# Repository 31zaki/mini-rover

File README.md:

# Rover mini Project

This project, named "rover-mini," is inspired by my favorite British car, the [Rover Mini](https://en.wikipedia.org/wiki/Mini). The name reflects my respect for this iconic vehicle, known for its compact design and efficient performance, traits that I aim to emulate in this mini robotic rover project.

## Project Overview
The Mini Rover is built using only the chassis of the PiCar-X. For detailed information about the PiCar-X chassis, you can refer to the [official documentation](https://docs.sunfounder.com/projects/picar-x-v20/en/latest/index.html). Note that in this project, the included Robot-HAT is not used. Instead, a custom PCB has been designed for the necessary components and connections. Additionally, custom parts for mounting the PCB were designed using Fusion360.

## Components

- **Raspberry Pi 4B** running Ubuntu Server 22.04 Jazzy.
- **Chassis:** PiCar-X (excluding Robot-HAT expansion board).
- **Cooling:** [GeeekPi Raspberry Pi Low Profile CPU Cooler](https://www.amazon.co.jp/-/en/GeeekPi-Raspberry-Profile-Compatible-Heatsink/dp/B082WV2LL7?th=1).
- **Battery:** [Battery for Raspberry Pi](https://www.amazon.co.jp/gp/product/B0C1GFX5LW/ref=ppx_yo_dt_b_asin_title_o00_s02?ie=UTF8&psc=1).
- **GPIO Expansion:** [GPIO Expansion Board](https://www.amazon.co.jp/gp/product/B072XBX3XX/ref=ppx_yo_dt_b_asin_title_o00_s01?ie=UTF8&th=1).
- **Breadboard** for initial wiring, with plans to design a custom PCB later.

## PCB Design

To streamline the wiring and improve reliability, a custom PCB has been designed using EAGLE. The PCB integrates all necessary components and connections for the Mini Rover.

### EAGLE Design Files

The PCB design files can be found in the `EAGLE/project` directory of this repository. This includes:
- Schematic file (`main_board.sch`)
- Board file (`main_board.brd`)

### EAGLE Libraries

Custom EAGLE libraries have been created for the components used in this project. These libraries are included in the `EAGLE/libraries` directory of this repository.

## Development Environment

**Programming Language:** Python
- **IDE:** Visual Studio Code (VSCode)
- **Connection:** SSH from VSCode to Raspberry Pi

## Wiring Information

### Raspberry Pi 4 (40-pin header) Connections
- **3.3V (Pin 1)** --------------- VCC (BNO055)
- **5V (Pin 2)** --------------- VCC (HC-SR04)
- **GND (Pin 6)** --------------- GND (L298N)
- **GND (Pin 9)** --------------- GND (BNO055)
- **GND (Pin 14)** -------------- GND (Servo Motors)
- **GPIO 2 (Pin 3)** ------------- SDA (BNO055)
- **GPIO 3 (Pin 5)** ------------- SCL (BNO055)
- **GPIO 4 (Pin 7)** ------------- ECHO (HC-SR04) through voltage divider
- **GPIO 17 (Pin 11)** ----------- TRIG (HC-SR04)
- **GPIO 18 (Pin 12)** ----------- ENA (L298N)
- **GPIO 23 (Pin 16)** ----------- IN2 (L298N)
- **GPIO 24 (Pin 18)** ----------- IN1 (L298N)
- **GPIO 25 (Pin 22)** ----------- ENB (L298N)
- **GPIO 27 (Pin 13)** ----------- IN3 (L298N)
- **GPIO 22 (Pin 15)** ----------- IN4 (L298N)
- **GPIO 5 (Pin 29)** ------------ Servo 1 Control
- **GPIO 6 (Pin 31)** ------------ Servo 2 Control
- **GPIO 13 (Pin 33)** ----------- Servo 3 Control

## Goals

- **Programming Practice:** Enhance programming skills, particularly in Python.
- **Electronics Practice:** Gain hands-on experience with electronics and hardware integration.
- **Autonomous Navigation:** Develop a rover that can navigate autonomously using GPS coordinates.
- **ARUCO Tag Recognition:** Implement ARUCO tag recognition for advanced navigation and positioning.

## Getting Started

### Prerequisites

Ensure you have the following installed on your Raspberry Pi:
- Python 3.x
- Git
- Any other dependencies as listed in the `requirements.txt` file (to be added later).

### Installation

Clone this repository to your Raspberry Pi:
    ```bash
    git clone https://github.com/31zaki/mini-rover.git
    cd mini-rover
    ```
Install the necessary Python packages:

Connect to your Raspberry Pi from VSCode via SSH to start development.

## Usage

Detailed usage instructions will be added here as the project progresses.

## Contributing

Contributions are welcome! Please create a fork of the repository, make your changes, and submit a pull request for review.

## License

This project is licensed under the MIT License. See the LICENSE file for details.

## Acknowledgments

- SunFounder for the PiCar-X chassis
- GeeekPi for the cooling solution
- [Battery Supplier](https://www.amazon.co.jp/gp/product/B0C1GFX5LW/ref=ppx_yo_dt_b_asin_title_o00_s02?ie=UTF8&psc=1) for the battery
- [GPIO Expansion Board Supplier](https://www.amazon.co.jp/gp/product/B072XBX3XX/ref=ppx_yo_dt_b_asin_title_o00_s01?ie=UTF8&th=1) for the GPIO expansion

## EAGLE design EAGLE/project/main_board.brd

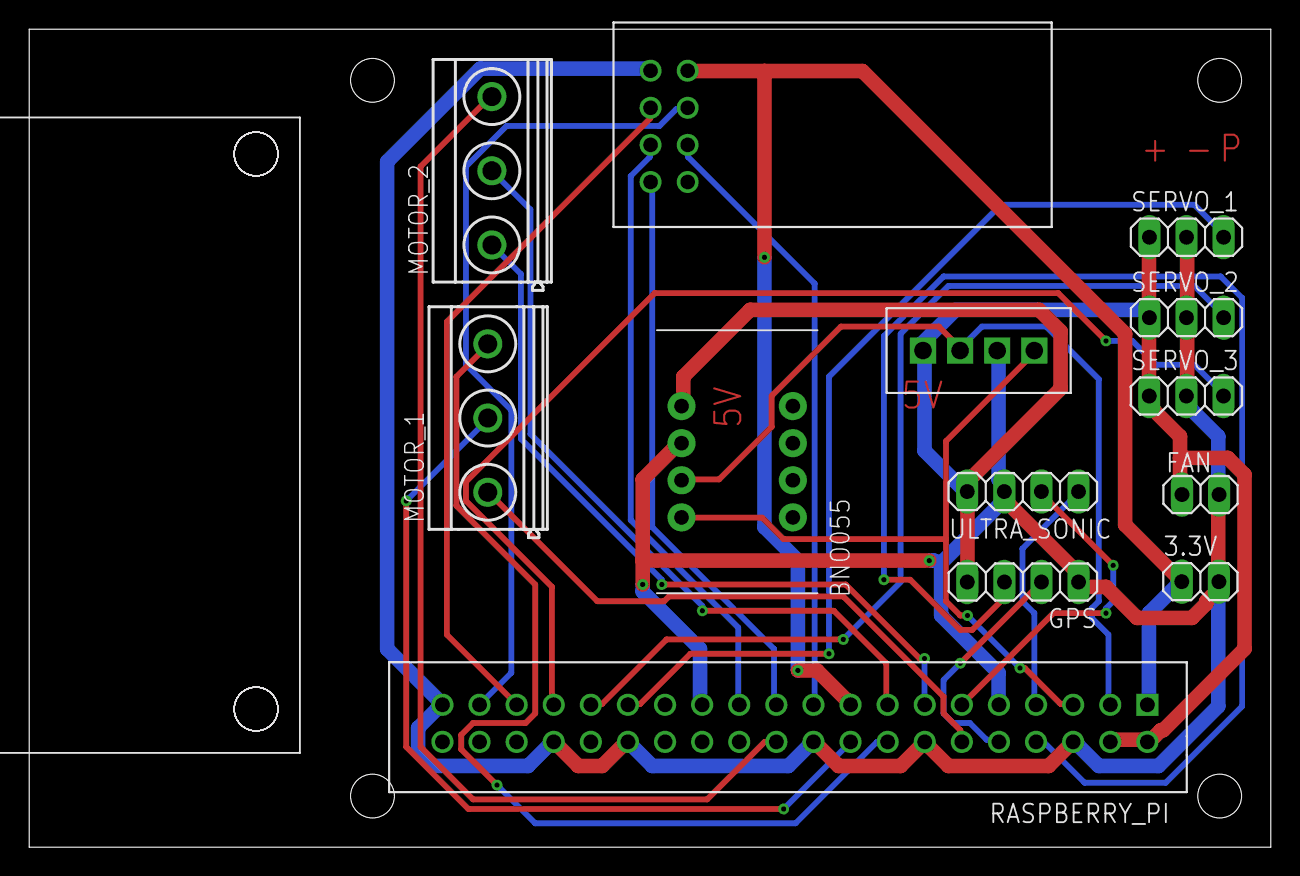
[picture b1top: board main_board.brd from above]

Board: 2 copper layers, 85.0 x 56.0 mm, 14 parts (0 on the bottom side), 23 nets.

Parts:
3.3V: 1X02
BNO055: 2472; MODULE_2472
FAN: 1X02
GPS: 1X04
L298N1: L298N_DRIVER
MOTOR_1, MOTOR_2: MKDSN1,5/3-5,08
NRF24L1: NRF24L01
RASPBERRY_PI: RASPBERRY_PI_4B_4GB; MODULE_RASPBERRY_PI_4B_4GB
SERVO_1, SERVO_2, SERVO_3: 1X03
U$1: DHT20
ULTRA_SONIC: 1X04

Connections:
3.3V: 3.3V.1, NRF24L1.VCC, RASPBERRY_PI.1, RASPBERRY_PI.17
5V: BNO055.VIN, FAN.1, GPS.4, RASPBERRY_PI.2, RASPBERRY_PI.4, SERVO_1.1, SERVO_2.1, SERVO_3.1, U$1.5V, ULTRA_SONIC.1
BNO055_SCL: BNO055.SCL, RASPBERRY_PI.5, U$1.SCL
BNO055_SDA: BNO055.SDA, RASPBERRY_PI.3, U$1.SDA
ENA: MOTOR_1.1, RASPBERRY_PI.12
ENB: MOTOR_2.3, RASPBERRY_PI.22
GND: 3.3V.2, BNO055.GND, FAN.2, GPS.1, NRF24L1.GND, RASPBERRY_PI.6, RASPBERRY_PI.9, RASPBERRY_PI.14, RASPBERRY_PI.20, RASPBERRY_PI.25, RASPBERRY_PI.30, RASPBERRY_PI.34, RASPBERRY_PI.39, SERVO_1.2, SERVO_2.2, SERVO_3.2, U$1.GND, ULTRA_SONIC.2
IN1: MOTOR_1.2, RASPBERRY_PI.18
IN2: MOTOR_1.3, RASPBERRY_PI.16
IN3: MOTOR_2.1, RASPBERRY_PI.13
IN4: MOTOR_2.2, RASPBERRY_PI.15
unnamed: NRF24L1.CE, RASPBERRY_PI.35
unnamed: NRF24L1.CSN, RASPBERRY_PI.37
unnamed: NRF24L1.SCK, RASPBERRY_PI.23
unnamed: NRF24L1.MOSI, RASPBERRY_PI.19
unnamed: NRF24L1.MISO, RASPBERRY_PI.21
PWM_SERVO_1: RASPBERRY_PI.29, SERVO_1.3
PWM_SERVO_2: RASPBERRY_PI.31, SERVO_2.3
PWM_SERVO_3: RASPBERRY_PI.33, SERVO_3.3
RX: GPS.3, RASPBERRY_PI.8
TX: GPS.2, RASPBERRY_PI.10
ULTRA_SONIC_1: RASPBERRY_PI.7, ULTRA_SONIC.4
ULTRA_SONIC_2: RASPBERRY_PI.11, ULTRA_SONIC.3

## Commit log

2024-06-12 first commit from raspberry pi
2024-06-12 remove main.py
2024-06-12 modified existed files (test)
2024-06-12 write README.md with GPT
2024-06-12 commit test from raspberry pi
2024-06-12 add motor_test.py
2024-06-12 add visualise_bno055_3d.py
2024-06-12 add bme280_sensor.py, but lookes there are some trouble
2024-06-12 modified BNO055 and BME280 code
2024-06-12 modified visualise_bno055_3d.py but couldn't plot 3d
2024-06-13 rearrange folder
2024-06-13 design main board PCB by EAGLE
2024-06-14 add files to control motors. motor_control.py worked.
2024-06-16 put the files right place
2024-06-17 update main board
2024-06-18 modify board dimension and add GPS module
2024-06-18 separate motor_control and motor_main
2024-06-20 add my script
2024-06-20 add communication and temp/humid sensor module
2024-06-20 add 3D model
2024-06-22 add motor_control.py and motor_main.py
